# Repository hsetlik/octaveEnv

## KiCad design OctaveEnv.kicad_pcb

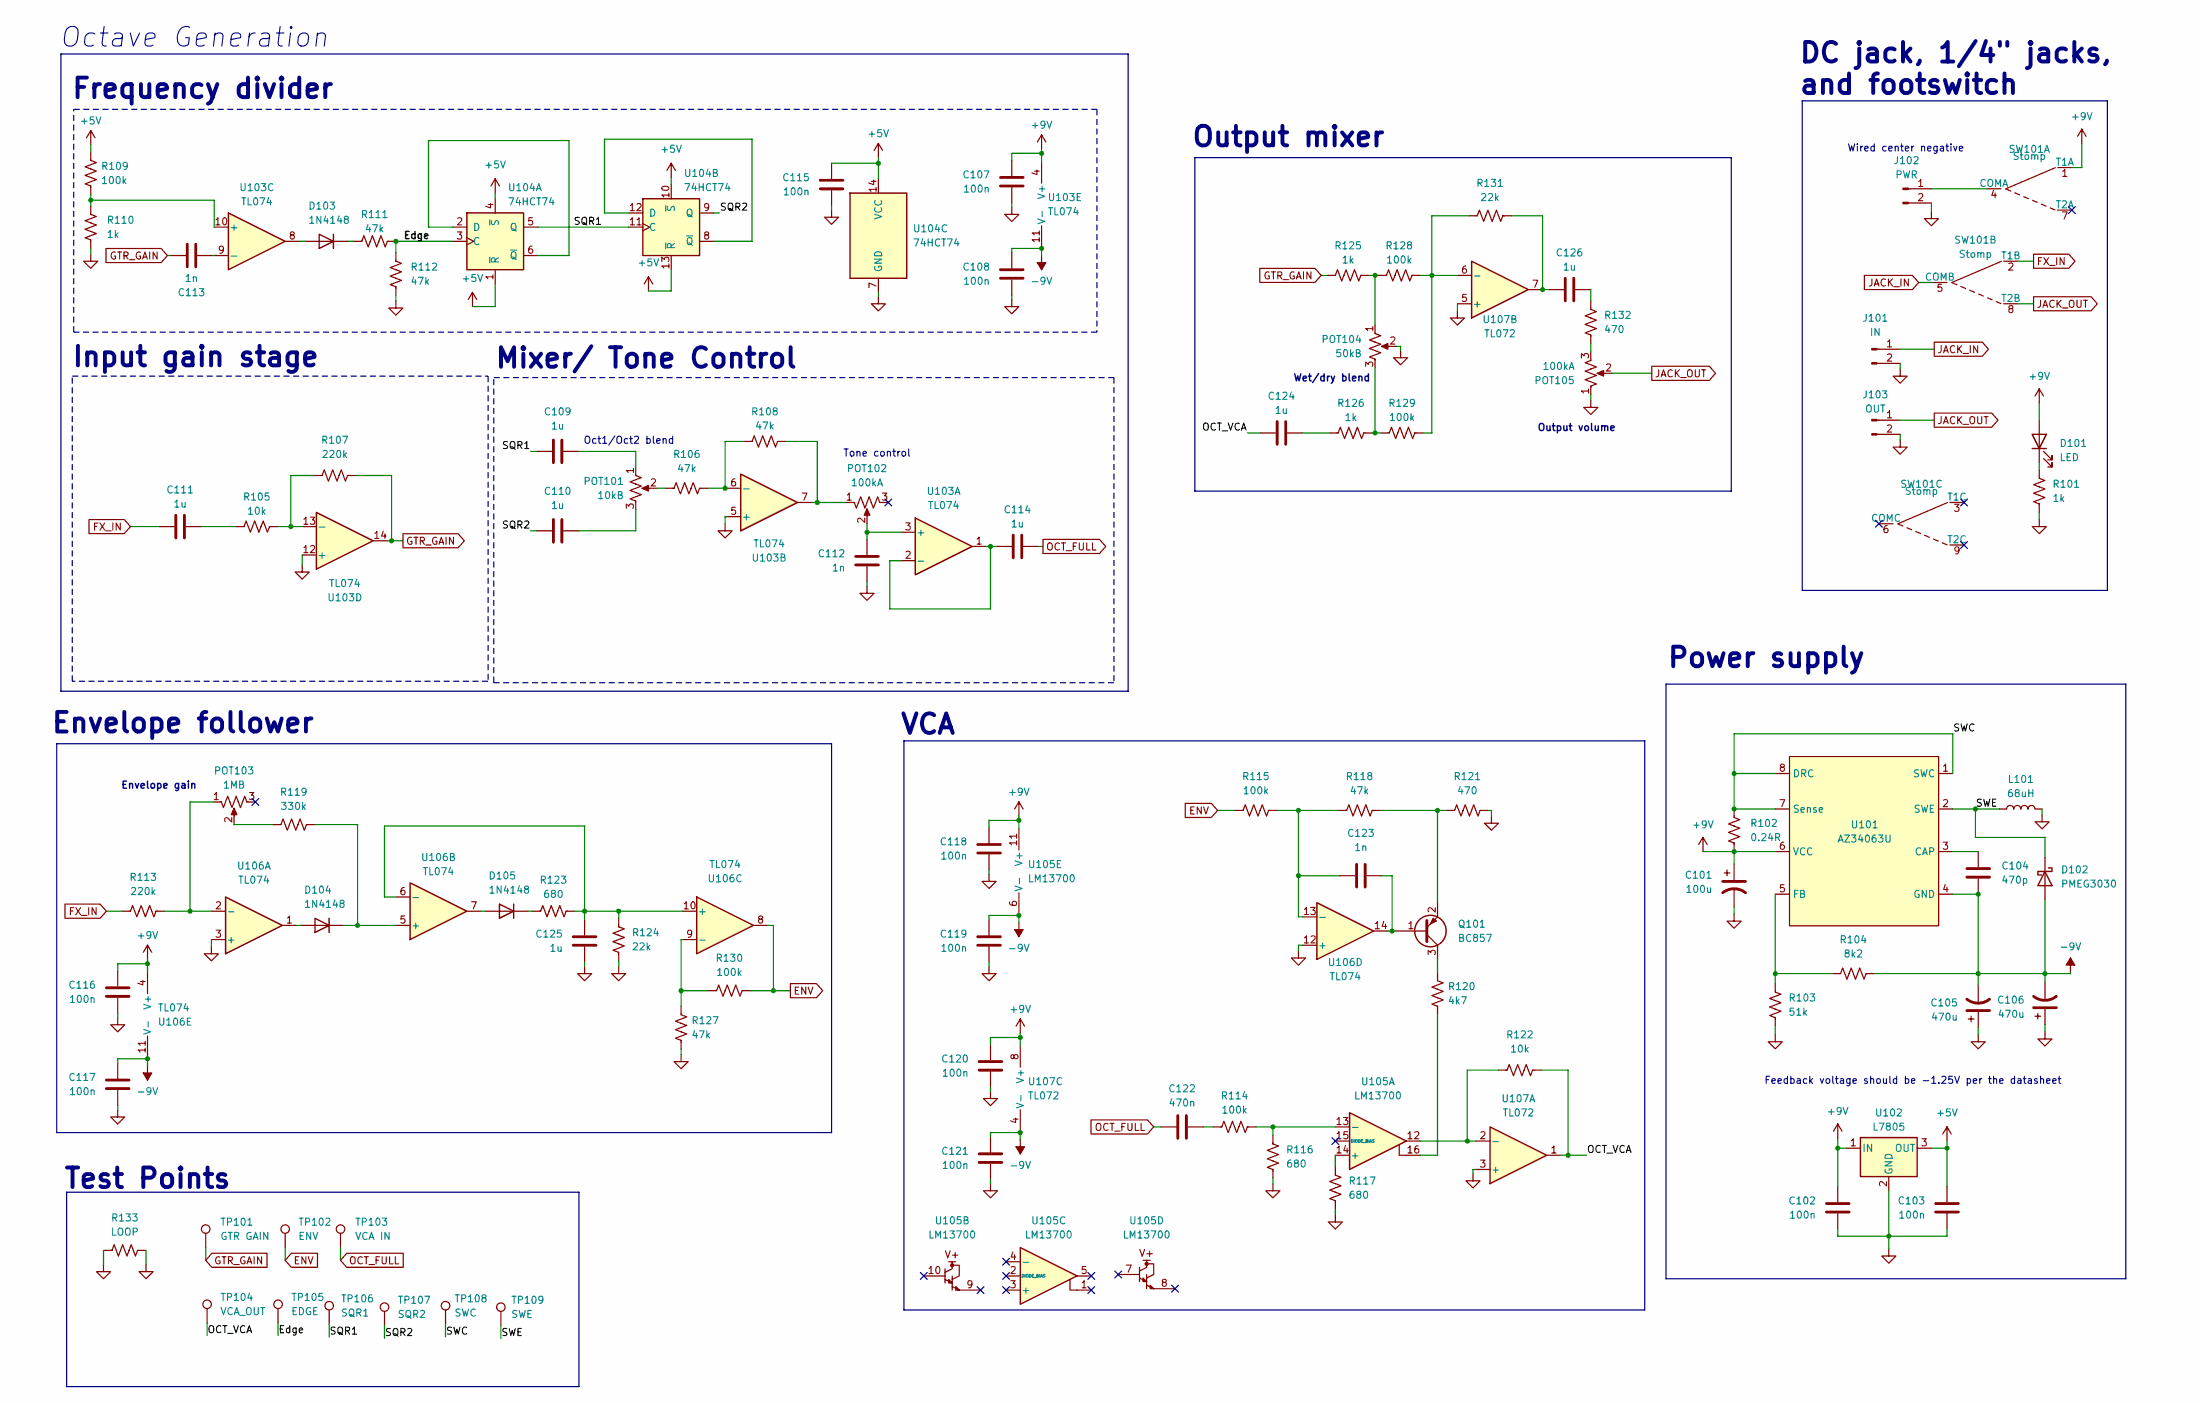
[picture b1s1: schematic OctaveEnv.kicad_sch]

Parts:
C101: 100u; CP_Radial_D5.0mm_P2.00mm
C102, C103, C107, C108, C115, C116, C117, C118, C119, C120, C121: 100n; C_0805_2012Metric
C104: 470p; C_0805_2012Metric
C105, C106: 470u; CP_Radial_D5.0mm_P2.00mm
C109, C110, C111, C114, C124, C125, C126: 1u; C_0805_2012Metric
C112, C113, C123: 1n; C_0805_2012Metric
C122: 470n; C_0805_2012Metric
D101: LED; LED_D3.0mm
D102: PMEG3030; D_SOD-123
D103, D104, D105: 1N4148; D_SOD-123
J101: IN; PinHeader_1x02_P2.54mm_Vertical
J102: PWR; PinHeader_1x02_P2.54mm_Vertical
J103: OUT; PinHeader_1x02_P2.54mm_Vertical
L101: 68uH; L_TDK_VLS6045EX_VLS6045AF
POT101: 10kB; Potentiometer_Alpha_RD901F-40-00D_Single_Vertical
POT102, POT105: 100kA; Potentiometer_Alpha_RD901F-40-00D_Single_Vertical
POT103: 1MB; Potentiometer_Alpha_RD901F-40-00D_Single_Vertical
POT104: 50kB; Potentiometer_Alpha_RD901F-40-00D_Single_Vertical
Q101: BC857; SOT-23
R101, R110, R125, R126: 1k; R_0805_2012Metric
R102: 0.24R; R_0805_2012Metric
R103: 51k; R_0805_2012Metric
R104: 8k2; R_0805_2012Metric
R105, R122: 10k; R_0805_2012Metric
R106, R108, R111, R112, R118, R127: 47k; R_0805_2012Metric
R107, R113: 220k; R_0805_2012Metric
R109, R114, R115, R128, R129, R130: 100k; R_0805_2012Metric
R116, R117, R123: 680; R_0805_2012Metric
R119: 330k; R_0805_2012Metric
R120: 4k7; R_0805_2012Metric
R121, R132: 470; R_0805_2012Metric
R124, R131: 22k; R_0805_2012Metric
R133: LOOP; R_Axial_DIN0207_L6.3mm_D2.5mm_P7.62mm_Horizontal
SW101: Stomp; StompSwitchBreakout_P200
TP101: GTR GAIN; TestPoint_THTPad_D1.5mm_Drill0.7mm_VAL
TP102: ENV; TestPoint_THTPad_D1.5mm_Drill0.7mm_VAL
TP103: VCA IN; TestPoint_THTPad_D1.5mm_Drill0.7mm_VAL
TP104: VCA_OUT; TestPoint_THTPad_D1.5mm_Drill0.7mm_VAL
TP105: EDGE; TestPoint_THTPad_D1.5mm_Drill0.7mm_VAL
TP106: SQR1; TestPoint_THTPad_D1.5mm_Drill0.7mm_VAL
TP107: SQR2; TestPoint_THTPad_D1.5mm_Drill0.7mm_VAL
TP108: SWC; TestPoint_THTPad_D1.5mm_Drill0.7mm_VAL
TP109: SWE; TestPoint_THTPad_D1.5mm_Drill0.7mm_VAL
U101: AZ34063U; SO-8_3.9x4.9mm_P1.27mm
U102: L7805; TO-220-3_Vertical
U103, U106: TL074; SOIC-14_3.9x8.7mm_P1.27mm
U104: 74HCT74; SO-14_3.9x8.65mm_P1.27mm
U105: LM13700; SOIC-16_3.9x9.9mm_P1.27mm
U107: TL072; SOIC-8_3.9x4.9mm_P1.27mm

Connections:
+5V: C103.1, C115.1, R109.1, U102.3 (OUT), U104.1 (~R), U104.4 (~S), U104.10 (~S), U104.13 (~R), U104.14 (VCC)
+9V: C101.1, C102.1, C107.1, C116.1, C118.1, C120.1, D101.2 (A), R102.1, SW101.1 (T1A), U101.6 (VCC), U102.1 (IN), U103.4 (V+), U105.11 (V+), U106.4 (V+), U107.8 (V+)
-9V: C104.2, C105.2, C106.2, C108.1, C117.1, C119.1, C121.1, D102.2 (A), R104.2, U101.4 (GND), U103.11 (V-), U105.6 (V-), U106.11 (V-), U107.4 (V-)
/Edge: R111.2, R112.1, TP105.1, U104.3 (C)
/OCT_VCA: C124.1, R122.2, TP104.1, U107.1
/SQR1: C109.1, TP106.1, U104.5 (Q), U104.11 (C)
/SQR2: C110.1, TP107.1, U104.9 (Q)
/SWC: R102.2, TP108.1, U101.1 (SWC), U101.7 (Sense), U101.8 (DRC)
/SWE: D102.1 (K), L101.1, TP109.1, U101.2 (SWE)
ENV: R115.1, R130.2, TP102.1, U106.8
FX_IN: C111.1, R113.1, SW101.2 (T1B)
GND: C101.2, C102.2, C103.2, C105.1, C106.1, C107.2, C108.2, C112.2, C115.2, C116.2, C117.2, C118.2, C119.2, C120.2, C121.2, C125.2, J101.2, J102.2, J103.2, L101.2, POT104.2, POT105.1, R101.1, R103.1, R110.2, R112.2, R116.2, R117.2, R121.2, R124.2, R127.2, R133.1, R133.2, U102.2 (GND), U103.5 (+), U103.12 (+), U104.7 (GND), U106.3 (+), U106.12 (+), U107.3 (+), U107.5 (+)
GTR_GAIN: C113.1, R107.2, R125.1, TP101.1, U103.14
JACK_IN: J101.1, SW101.5 (COMB)
JACK_OUT: J103.1, POT105.2, SW101.8 (T2B)
unnamed: C109.2, POT101.1
unnamed: C110.2, POT101.3
unnamed: C111.2, R105.1
unnamed: C122.2, R114.1
unnamed: C124.2, R126.1
unnamed: C126.1, R131.2, U107.7
unnamed: C126.2, R132.1
unnamed: D101.1 (K), R101.2
unnamed: D103.2 (A), U103.8
unnamed: D103.1 (K), R111.1
unnamed: D104.2 (A), U106.1
unnamed: D104.1 (K), R119.2, U106.5 (+)
unnamed: D105.2 (A), U106.7
unnamed: D105.1 (K), R123.1
unnamed: J102.1, SW101.4 (COMA)
unnamed: POT101.2, R106.1
unnamed: POT102.1, R108.2, U103.7
unnamed: POT103.2, R119.1
unnamed: POT104.1, R125.2, R128.1
unnamed: POT104.3, R126.2, R129.1
unnamed: POT105.3, R132.2
unnamed: C123.2, Q101.1 (B), U106.14
unnamed: Q101.3 (C), R120.1
unnamed: Q101.2 (E), R118.2, R121.1
unnamed: R120.2, U105.16
unnamed: C104.1, U101.3 (CAP)
unnamed: R103.2, R104.1, U101.5 (FB)
unnamed: C112.1, POT102.2, U103.3 (+)
unnamed: C114.1, U103.1, U103.2 (-)
unnamed: R106.2, R108.1, U103.6 (-)
unnamed: R109.2, R110.1, U103.10 (+)
unnamed: C113.2, U103.9 (-)
unnamed: R105.2, R107.1, U103.13 (-)
unnamed: U104.2 (D), U104.6 (~Q)
unnamed: U104.8 (~Q), U104.12 (D)
unnamed: R117.1, U105.14 (+)
unnamed: R114.2, R116.1, U105.13 (-)
unnamed: POT103.1, R113.2, U106.2 (-)
unnamed: C125.1, R123.2, R124.1, U106.6 (-), U106.10 (+)
unnamed: R127.1, R130.1, U106.9 (-)
unnamed: C123.1, R115.2, R118.1, U106.13 (-)
unnamed: R122.1, U105.12, U107.2 (-)
unnamed: R128.2, R129.2, R131.1, U107.6 (-)
OCT_FULL: C114.2, C122.1, TP103.1

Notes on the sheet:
DC jack, 1/4" jacks, and footswitch
Envelope follower
Tone control
Output volume
Feedback voltage should be -1.25V per the datasheet
Frequency divider
Wet/dry blend
Octave Generation
Mixer/ Tone Control
Input gain stage
Envelope gain
VCA
Output mixer
Power supply
Test Points
Wired center negative
Oct1/Oct2 blend

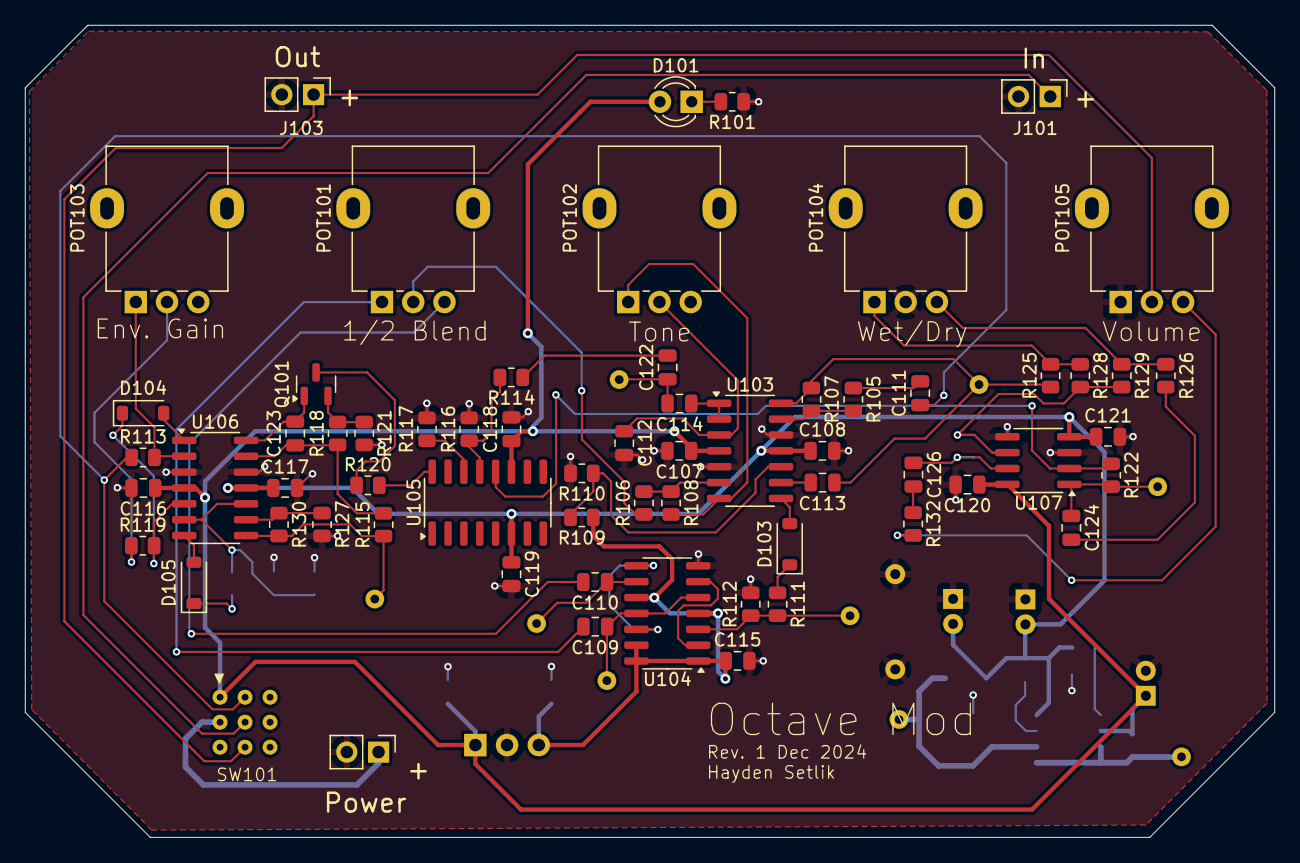
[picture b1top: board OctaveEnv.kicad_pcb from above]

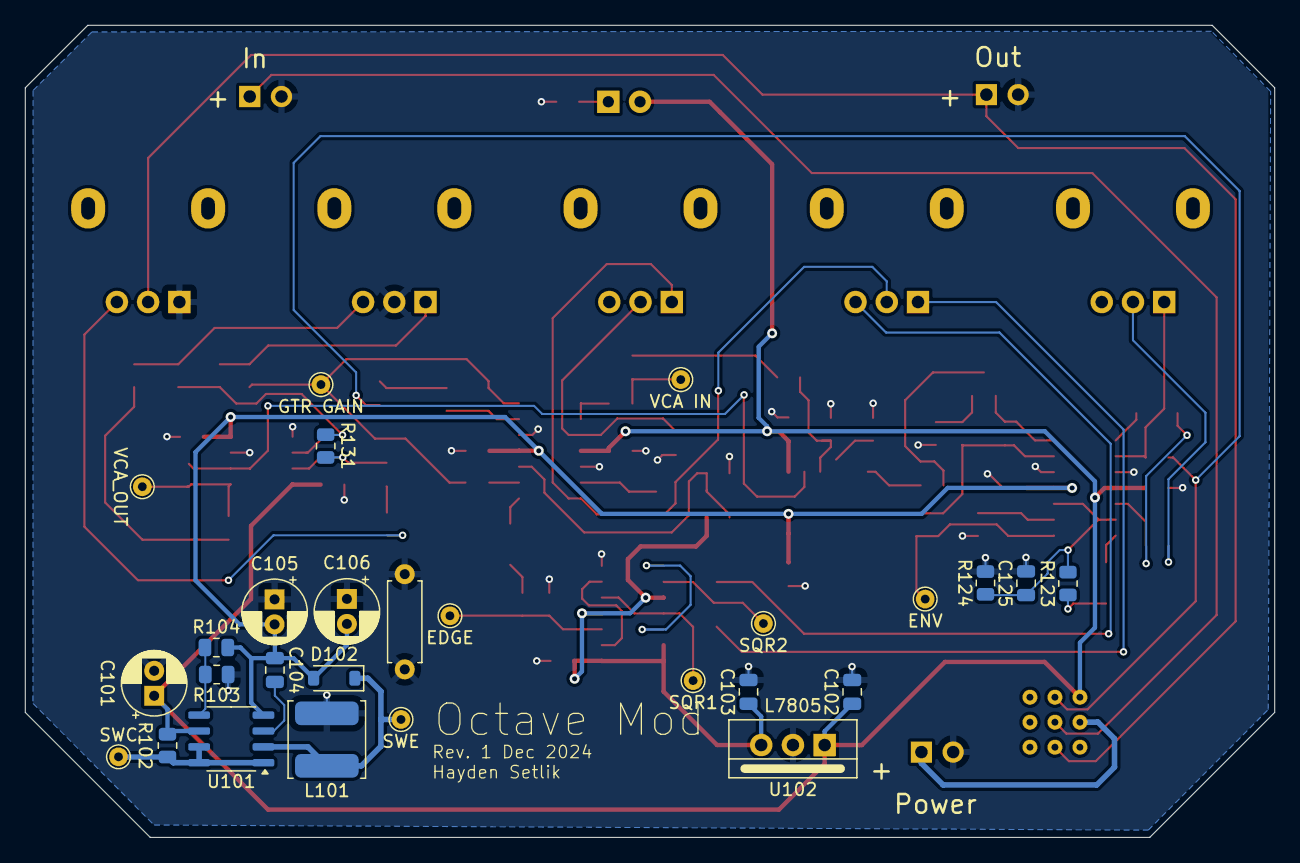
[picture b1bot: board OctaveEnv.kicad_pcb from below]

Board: 4 copper layers, 100.0 x 65.0 mm, 91 parts (27 on the bottom side), 59 nets.

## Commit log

2024-12-02 spice sim, start of schematic
2024-12-03 finished and consolidated schem
2024-12-03 footprints assigned, ERC passing
2024-12-04 layout start
2024-12-06 layout done
2024-12-06 routing and test points
2024-12-07 smaller outline
2024-12-07 silkscreen stuff, new layout
2024-12-07 new routing started
2024-12-07 routing done, DRC passing
2024-12-07 rev1 gerbers ready
2024-12-08 rev1 sent to fab
2024-12-10 added bom
2025-01-12 octave up sim
